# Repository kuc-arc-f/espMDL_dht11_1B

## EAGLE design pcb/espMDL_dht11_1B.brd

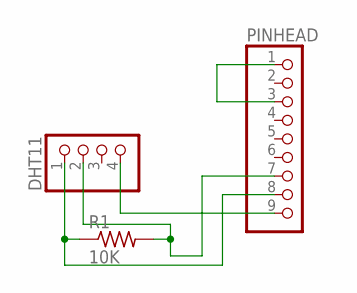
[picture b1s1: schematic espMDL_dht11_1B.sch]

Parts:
DHT11: PINHD-1X4; 1X04
PINHEAD: PINHD-1X9; 1X09
R1: 10K; 0204/7

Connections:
unnamed: DHT11.4, PINHEAD.9
unnamed: DHT11.1, PINHEAD.8, R1.1
unnamed: PINHEAD.1, PINHEAD.3
unnamed: DHT11.2, PINHEAD.7, R1.2

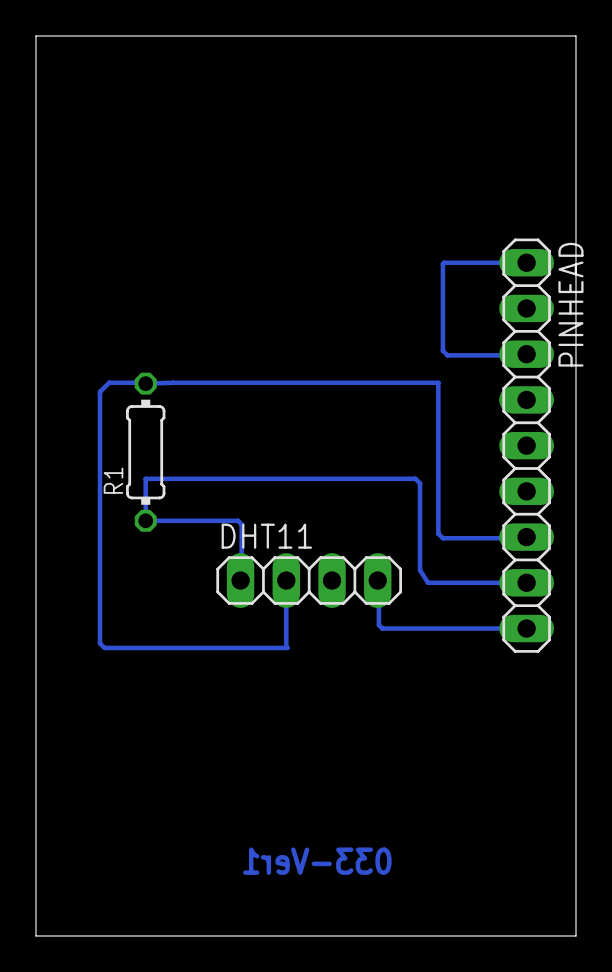
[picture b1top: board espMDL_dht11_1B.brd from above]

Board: 2 copper layers, 30.0 x 50.0 mm, 3 parts (0 on the bottom side), 4 nets.

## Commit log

2016-10-18 new, 10-18A2
2017-08-20 new, 08-20a1
